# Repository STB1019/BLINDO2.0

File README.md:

# BLINDO
## An IEEE STB1019 Project

Blindo is an open source project made by the members of **IEEE Student Branch 1019**
from Brescia University (Università degli Studi di Brescia) in collaboration 
with the organization (**Informatici Senza Frontiere**)[https://www.informaticisenzafrontiere.org/].

The objective of the project is the planning an engineerization of a support 
device for blind people to supplement theaching in the young age.

_Copyright (c) 2023 IEEE STB 1019. All rights reserved_

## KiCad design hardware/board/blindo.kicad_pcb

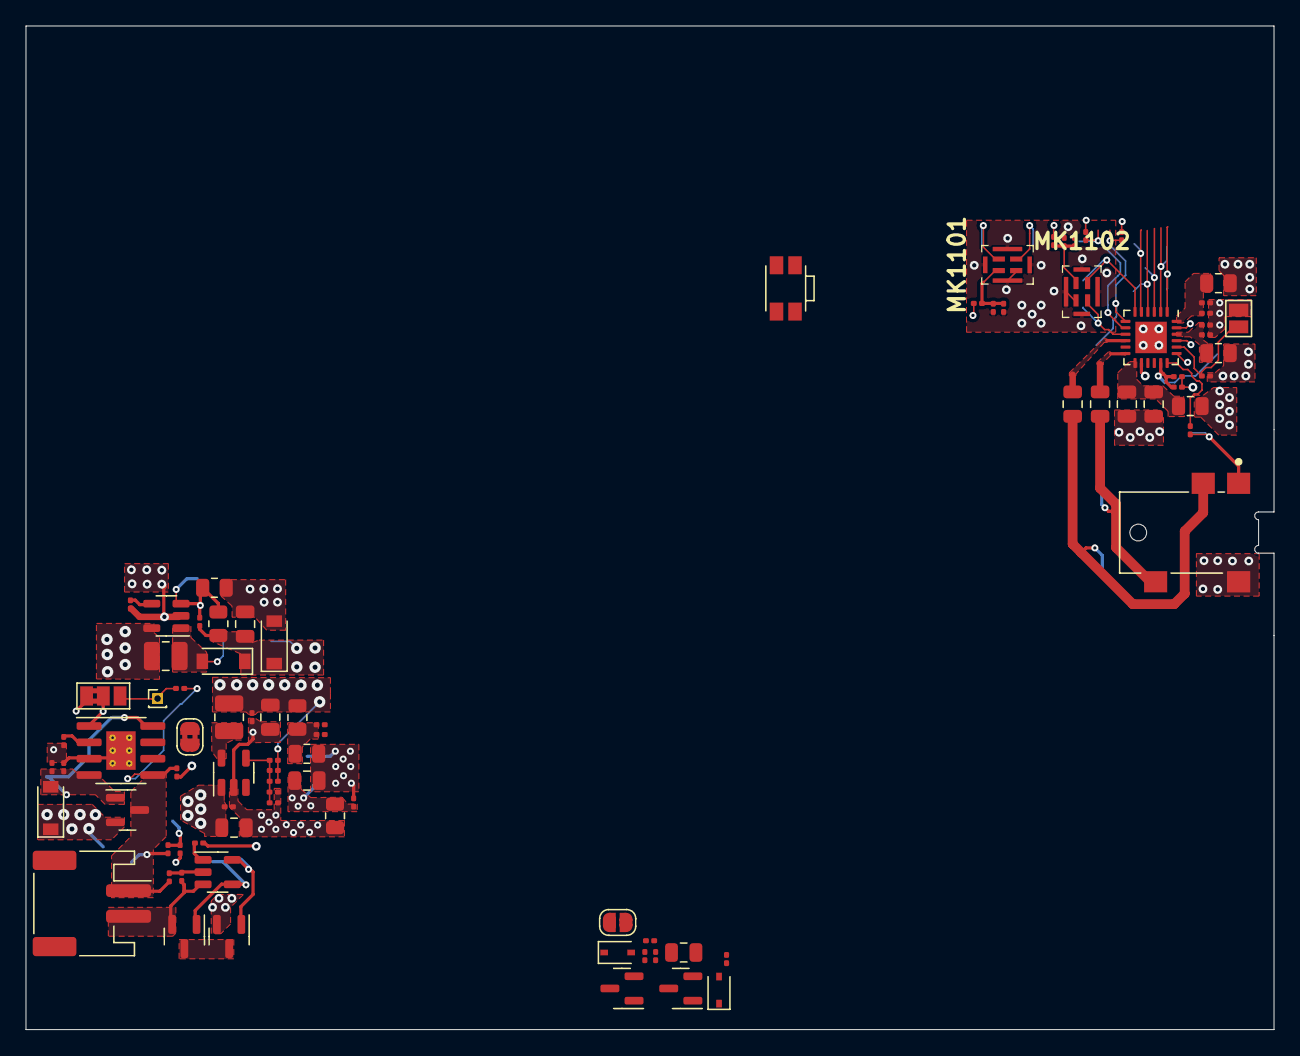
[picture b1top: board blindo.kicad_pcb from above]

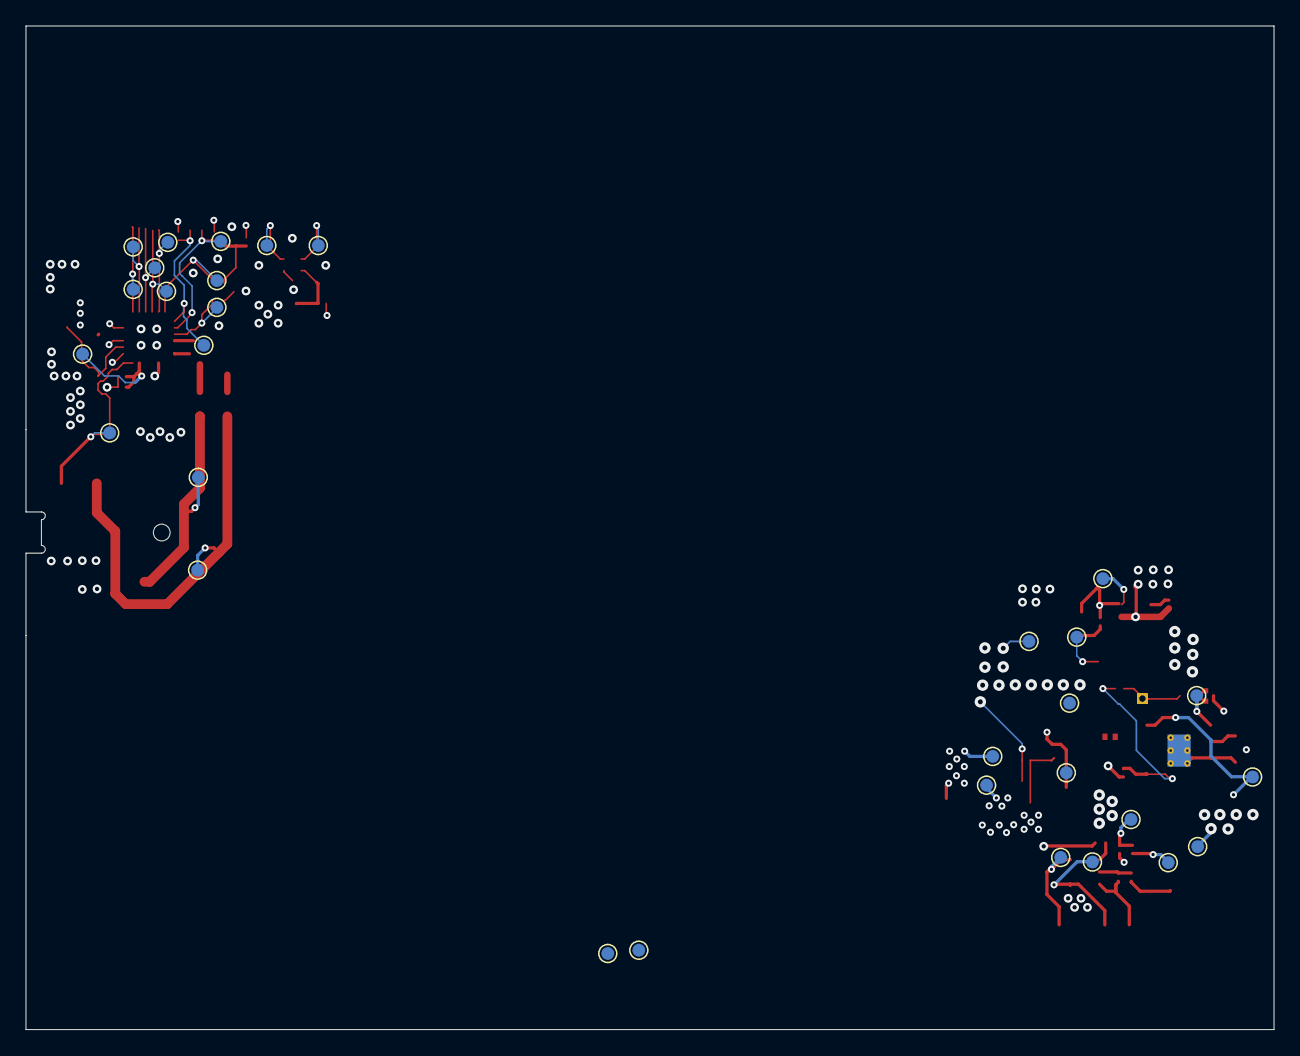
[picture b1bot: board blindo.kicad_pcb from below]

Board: 4 copper layers, 97.0 x 78.0 mm, 117 parts (31 on the bottom side), 54 nets.

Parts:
BT401: LiPo 3.7V; JST_PH_S2B-PH-SM4-TB_1x02-1MP_P2.00mm_Horizontal
C401, C402, C403, C602, C604, C605, C606, C701, C702, C703, C1102, C1104, C1106, C1107, C1111: 100n 0603; C_0201_0603Metric
C601, C607, C704, C902: 10u 0805; C_0805_2012Metric
C603, C1108, C1109: 47u 0805; C_0805_2012Metric
C901: 68p 0603; C_0201_0603Metric
C1101, C1103, C1105, C1110, C1112: 22u 0603; C_0201_0603Metric
C1113: 22u 0805; C_0805_2012Metric
C1114: 100n 0805; C_0805_2012Metric
D401, D901, D902: B5819W; D_SOD-123
D601, D602: 1N5819WS; D_SOD-323
FB701: 600R@100MHz 0805; R_0805_2012Metric
J1101: SJ2-35954A-SMT-TR; CUI_SJ2-35954A-SMT-TR
JP401: SolderJumper_3_Bridged12; SolderJumper-3_P1.3mm_Bridged2Bar12_Pad1.0x1.5mm_NumberLabe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
JP601: SolderJumper_2_Bridged; SolderJumper-2_P1.3mm_Bridged2Bar_RoundedPad1.0x1.5mm
JP602: SolderJumper_2_Open; SolderJumper-2_P1.3mm_Open_RoundedPad1.0x1.5mm
JP1101: SolderJumper_2_Open; SolderJumper-2_P1.3mm_Open_Pad1.0x1.5mm
L601, L901: LQH2HPZ6R8MJRL; L_1008_2520Metric
MK1101, MK1102: MP34DT05TR-A; MP34DT05TRA
NTC401: NP; PinHeader_1x01_P1.00mm_Vertical
Q401, Q602: AO3401A; SOT-23
Q402, Q403, Q601: AO3400A; SOT-23
R401, R402, R405, R407, R601, R602, R607, R901, R1102, R1103, R1104: 10K 0603; R_0201_0603Metric
R403: 330 0603; R_0201_0603Metric
R404, R406: 2K7 0603; R_0201_0603Metric
R603: 100K 0603; R_0201_0603Metric
R604, R1101, R1105: 0R 0603; R_0201_0603Metric
R605: 13K 0603; R_0201_0603Metric
R606: 5K1 0603; R_0201_0603Metric
R701: 10R 0805; R_0805_2012Metric
R702, R1106, R1108, R1109: 0R 0805; R_0805_2012Metric
R902: 82k 0805; R_0805_2012Metric
R903: 10k 0805; R_0805_2012Metric
R1107: 2K2 0603; R_0201_0603Metric
SW601: EVQP7A01P; SW_SPST_EVQP7A
TP401, TP402, TP403, TP404, TP405, TP406, TP407, TP601, TP602, TP603, TP604, TP701, TP702, TP901, TP902, TP903, TP1101, TP1102, TP1103, TP1104, TP1105, TP1106, TP1107, TP1108, TP1109, TP1110, TP1111, TP1112, TP1113, TP1114, TP1115: TestPoint_Small; TestPoint_Pad_D1.0mm
U401: AP9101CK-ETRG1; SOT-23-5
U402: TP4056; SOIC-8-1EP_3.9x4.9mm_P1.27mm_EP2.29x3mm_ThermalVias
U601: LM3671 1.8/ADJ; TSOT-23-5
U901: TPS61040DBV; SOT-23-5
U1101: TLV320DAC3203RGE; VQFN-24-1EP_4x4mm_P0.5mm_EP2.45x2.45mm

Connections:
+BATT: BT401.1 (+), C402.1, Q401.3 (D), R401.2, R403.1, R407.2, TP404.1, U402.5 (BAT)
-BATT: BT401.2 (-), C401.2, Q402.2 (S), U401.3 (VSS)
/Schema Funzionale/Audio Input-Output/BCLK: TP1106.1, U1101.2 (BCLK)
/Schema Funzionale/Audio Input-Output/DAC_AVCC: C1113.1, C1114.1, R1106.2, U1101.13 (AVDD)
/Schema Funzionale/Audio Input-Output/DAC_DVCC: C1111.1, C1112.1, R1108.2, U1101.22 (DVDD)
/Schema Funzionale/Audio Input-Output/DAC_IOVCC: C1107.1, C1110.1, R1109.2, U1101.24 (IOVDD)
/Schema Funzionale/Audio Input-Output/DAC_REF: C1105.1, C1106.1, TP1112.1, U1101.17 (REF)
/Schema Funzionale/Audio Input-Output/DAT: TP1108.1, U1101.4 (DIN)
/Schema Funzionale/Audio Input-Output/DMIC_CLK: MK1102.1 (CLK), TP1111.1, U1101.9 (DMIC_CLK)
/Schema Funzionale/Audio Input-Output/DMIC_DAT: MK1102.2 (DOUT), TP1110.1, U1101.6 (DMIC_IN)
/Schema Funzionale/Audio Input-Output/L_CH: C1109.2, J1101.T, TP1114.1
/Schema Funzionale/Audio Input-Output/L_CH_OUT: C1109.1, U1101.12 (LHP)
/Schema Funzionale/Audio Input-Output/MCLK: TP1105.1, U1101.1 (MCLK)
/Schema Funzionale/Audio Input-Output/MICBIAS: R1107.1, U1101.18 (MIC_BIAS)
/Schema Funzionale/Audio Input-Output/MIC_AVCC: C1103.1, C1104.1, MK1102.3 (VDD), R1105.2
/Schema Funzionale/Audio Input-Output/MIC_AVCC_2: C1101.1, C1102.1, MK1101.3 (VDD), R1101.2
/Schema Funzionale/Audio Input-Output/PDM.CLK: MK1101.1 (CLK), TP1101.1
/Schema Funzionale/Audio Input-Output/PDM.DAT: MK1101.2 (DOUT), TP1102.1
/Schema Funzionale/Audio Input-Output/RECV: TP1109.1, U1101.5 (DOUT)
/Schema Funzionale/Audio Input-Output/R_CH: C1108.2, J1101.R1, TP1113.1
/Schema Funzionale/Audio Input-Output/R_CH_OUT: C1108.1, U1101.10 (RHP)
/Schema Funzionale/Audio Input-Output/SCL: R1102.2, TP1103.1, U1101.7 (SCL/~SS)
/Schema Funzionale/Audio Input-Output/SDA: R1103.2, TP1104.1, U1101.8 (SDA/MOSI)
/Schema Funzionale/Audio Input-Output/SLEEVE_OUT: J1101.S, R1107.2, TP1115.1
/Schema Funzionale/Audio Input-Output/WCLK: TP1107.1, U1101.3 (WCLK)
/Schema Funzionale/Audio Input-Output/~DAC_RST: JP1101.2 (B), R1104.2, U1101.20 (~RST)
/Schema Funzionale/Power Rails/Analog Filter/VDDA_PRE: C701.1, C702.1, FB701.1, R701.1
/Schema Funzionale/Power Rails/Gestione Batteria/BAT_NTC: JP401.3 (B), NTC401.1, R407.1
/Schema Funzionale/Power Rails/Gestione Batteria/BAT_PROT_VCC: C401.1, R403.2, U401.2 (VDD)
/Schema Funzionale/Power Rails/Gestione Batteria/BAT_PRT_VM: R404.2, U401.1 (VM)
/Schema Funzionale/Power Rails/Gestione Batteria/CHRG: JP601.1 (A), U402.7 (~CHRG)
/Schema Funzionale/Power Rails/Gestione Batteria/CHRG_EN: Q403.1 (G), TP406.1, U401.5 (CO)
/Schema Funzionale/Power Rails/Gestione Batteria/DSCH_EN: Q402.1 (G), TP405.1, U401.4 (DO)
/Schema Funzionale/Power Rails/Gestione Batteria/I_CHRG: R406.2, U402.2 (PROG)
/Schema Funzionale/Power Rails/Gestione Batteria/NTC_REF: JP401.2 (C), TP407.1, U402.1 (TEMP)
/Schema Funzionale/Power Rails/LCD_EN: R901.1, U901.4 (EN)
/Schema Funzionale/Power Rails/LCD_Regulator/VLCD_FB: C901.2, R902.1, R903.2, TP903.1, U901.3 (FB)
/Schema Funzionale/Power Rails/LCD_Regulator/VLCD_SW: D901.2 (A), L901.2, TP901.1, U901.1 (SW)
/Schema Funzionale/Power Rails/Main Reglator/VREG_FB: C604.2, C605.1, R604.1, R605.2, R606.1, TP603.1, U601.4 (FB)
/Schema Funzionale/Power Rails/Main Reglator/VREG_SW: L601.1, U601.5 (SW)
/Schema Funzionale/Power Rails/PWR_BTN_SENSE: D601.2 (A), R607.1
/Schema Funzionale/Power Rails/VBASE: C601.1, C602.1, D401.1 (K), JP602.2 (B), L901.1, Q401.2 (S), R601.1, R603.1, TP402.1, U601.1 (Vin), U901.5 (VIN)
/Schema Funzionale/Power Rails/VBAT: R401.1, R402.2, TP401.1
/Schema Funzionale/Power Rails/VIN: C403.1, D401.2 (A), Q401.1 (G), R405.2, TP403.1, U402.4 (VCC), U402.8 (CE)
/Schema Funzionale/Power Rails/VLCD: C901.1, C902.1, D901.1 (K), D902.1 (K), R902.2, TP902.1
GND: C402.2, C403.2, C601.2, C602.2, C603.2, C605.2, C606.2, C607.2, C701.2, C702.2, C902.2, C1107.2, C1110.2, C1111.2, C1112.2, D902.2 (A), JP401.1 (A), JP1101.1 (A), Q403.2 (S), Q601.2 (S), R402.1, R404.1, R405.1, R406.1, R606.2, R702.2, R901.2, R903.1, SW601.1, U402.3 (GND), U402.9 (EP), U601.2 (GND), U901.2 (GND), U1101.19 (SPISEL), U1101.21 (DGND), U1101.23 (IOGND)
GNDA: C703.2, C704.2, C1101.2, C1102.2, C1103.2, C1104.2, C1105.2, C1106.2, C1113.2, C1114.2, J1101.R2, MK1101.4 (LR), MK1101.5 (GND_1), MK1101.6 (GND_2), MK1101.7 (GND_3), MK1101.8 (GND_4), MK1102.4 (LR), MK1102.5 (GND_1), MK1102.6 (GND_2), MK1102.7 (GND_3), MK1102.8 (GND_4), R702.1, TP701.1, U1101.14 (AGND), U1101.25 (PAD)
unnamed: C603.1, D602.1 (K), JP602.1 (A), Q602.3 (D), R602.1, TP602.1, U601.3 (EN)
unnamed: D601.1 (K), JP601.2 (B), Q601.1 (G), Q602.1 (G), R601.2, SW601.2, TP601.1
unnamed: Q402.3 (D), Q403.3 (D)
unnamed: Q601.3 (D), R602.2
unnamed: Q602.2 (S), R603.2
VCC: C604.1, C606.1, C607.1, L601.2, R604.2, R605.1, R607.2, R701.2, R1102.1, R1103.1, R1104.1, R1108.1, R1109.1, TP604.1
VDDA: C703.1, C704.1, FB701.2, R1101.1, R1105.1, R1106.1, TP702.1

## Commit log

2023-02-16 First work hardware side
